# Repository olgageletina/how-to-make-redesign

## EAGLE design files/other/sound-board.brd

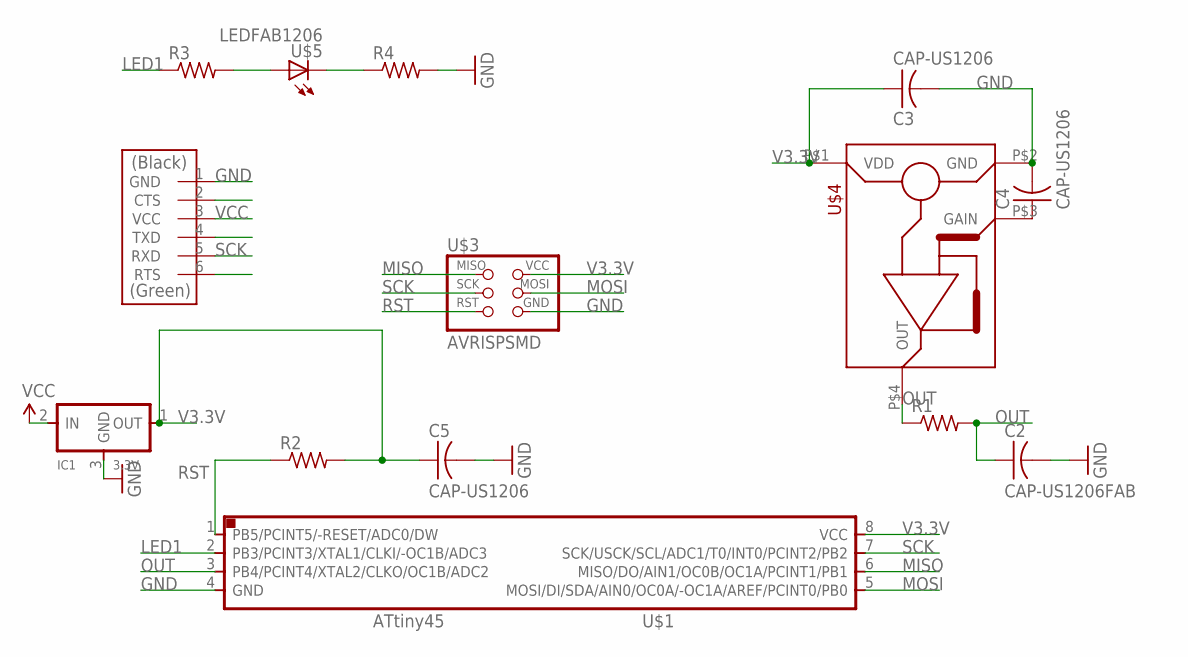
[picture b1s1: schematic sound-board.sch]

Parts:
C2: CAP-US1206FAB; C1206FAB
C3, C4, C5: CAP-US1206; C1206
IC1: 3.3V; SOT23
R1, R2: RES-US1206; R1206
R3, R4: RES-US1206FAB; R1206FAB
U$1: ATTINY45SI; SOIC8
U$2: FTDI-SMD-HEADER; 1X06SMD
U$3: AVRISPSMD; 2X03SMD
U$4: MEMS_MIC_SPU0414HR5H-SB; CSP-4PIN
U$5: LEDFAB1206; LED1206FAB

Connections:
GAIN: C4.1, U$4.P$3 (GAIN)
GND: C2.2, C3.2, C4.2, C5.2, IC1.3 (GND), R4.2, U$1.4 (GND), U$2.1 (GND), U$3.6 (GND), U$4.P$2 (GND)
LED1: R3.1, U$1.2 (PB3/PCINT3/XTAL1/CLKI/-OC1B/ADC3)
MISO: U$1.6 (MISO/DO/AIN1/OC0B/OC1A/PCINT1/PB1), U$3.1 (MISO)
MOSI: U$1.5 (MOSI/DI/SDA/AIN0/OC0A/-OC1A/AREF/PCINT0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), U$3.4 (MOSI)
unnamed: R3.2, U$5.1 (A)
unnamed: R4.1, U$5.2 (C)
OUT: C2.1, R1.1, R1.2, U$1.3 (PB4/PCINT4/XTAL2/CLKO/OC1B/ADC2), U$4.P$4 (OUT)
RST: R2.1, U$1.1 (PB5/PCINT5/-RESET/ADC0/DW), U$3.5 (RST)
SCK: U$1.7 (SCK/USCK/SCL/ADC1/T0/INT0/PCINT2/PB2), U$2.5 (RXD), U$3.3 (SCK)
V3.3V: C3.1, C5.1, IC1.1 (OUT), R2.2, U$1.8 (VCC), U$3.2 (VCC), U$4.P$1 (VDD)
VCC: IC1.2 (IN), U$2.3 (VCC)

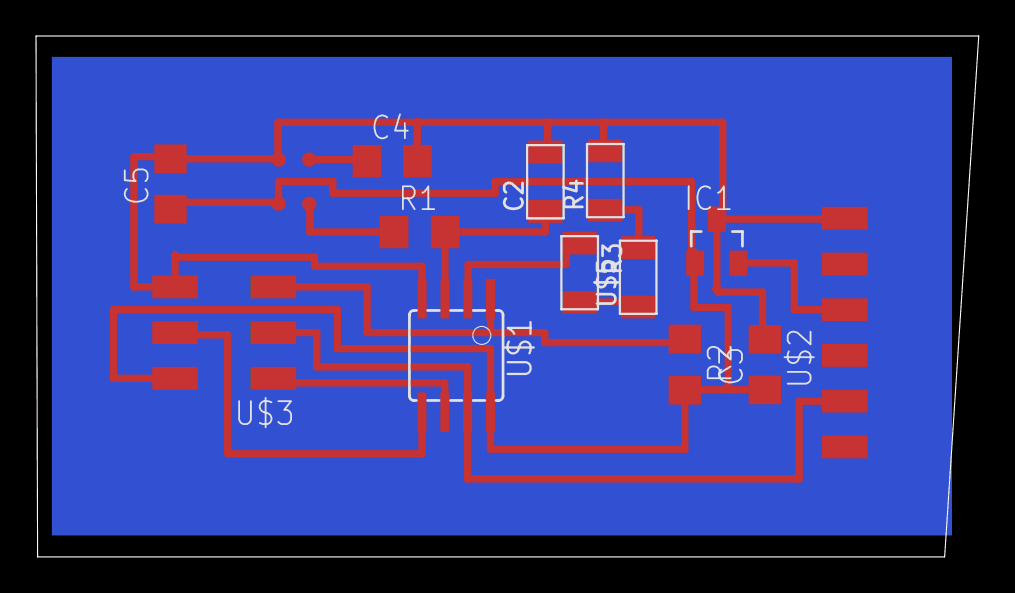
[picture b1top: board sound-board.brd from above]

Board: 2 copper layers, 52.4 x 28.9 mm, 14 parts (0 on the bottom side), 12 nets.

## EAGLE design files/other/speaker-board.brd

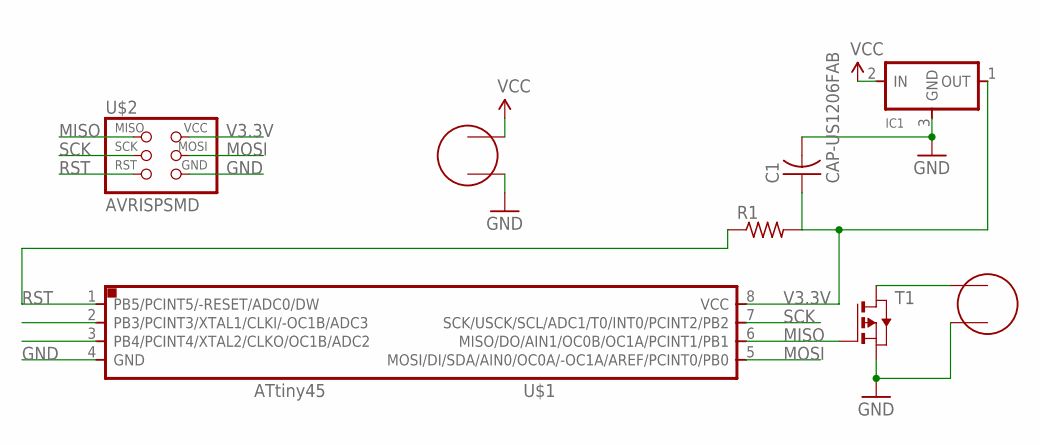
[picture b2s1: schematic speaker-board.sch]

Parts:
C1: CAP-US1206FAB; C1206FAB
IC1: REGULATORSOT23; SOT23
R1: RES-US1206FAB; R1206FAB
T1: PMOSFETSOT23; SOT-23
U$1: ATTINY45SI; SOIC8
U$2: AVRISPSMD; 2X03SMD
U$3, U$4: PINHD-2X1-SMD; 2X01SMD

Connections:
GND: C1.2, IC1.3 (GND), T1.2 (S), U$1.4 (GND), U$2.6 (GND), U$3.4, U$4.3
MISO: T1.3 (G), U$1.6 (MISO/DO/AIN1/OC0B/OC1A/PCINT1/PB1), U$2.1 (MISO)
MOSI: U$1.5 (MOSI/DI/SDA/AIN0/OC0A/-OC1A/AREF/PCINT0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), U$2.4 (MOSI)
unnamed: T1.1 (D), U$3.3
RST: R1.1, U$1.1 (PB5/PCINT5/-RESET/ADC0/DW), U$2.5 (RST)
SCK: U$1.7 (SCK/USCK/SCL/ADC1/T0/INT0/PCINT2/PB2), U$2.3 (SCK)
V3.3V: C1.1, IC1.1 (OUT), R1.2, U$1.8 (VCC), U$2.2 (VCC)
VCC: IC1.2 (IN), U$4.4

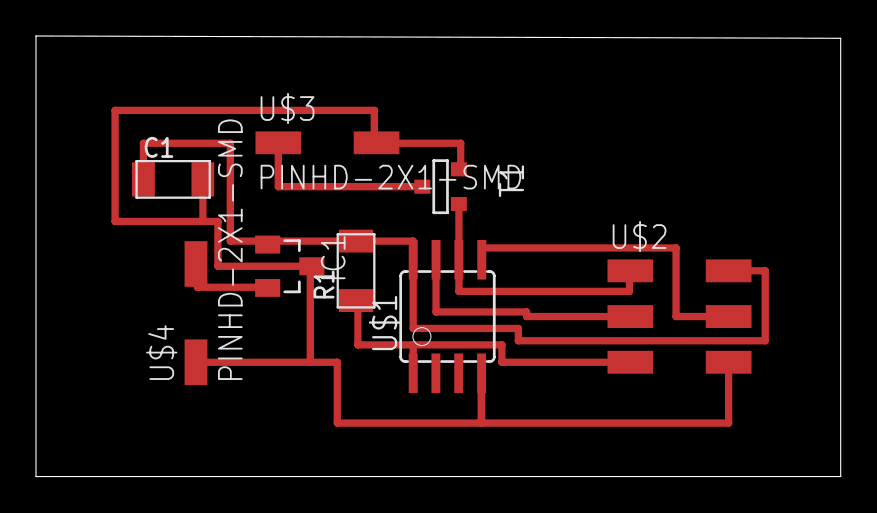
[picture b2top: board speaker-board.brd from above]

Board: 2 copper layers, 44.7 x 24.5 mm, 8 parts (0 on the bottom side), 8 nets.

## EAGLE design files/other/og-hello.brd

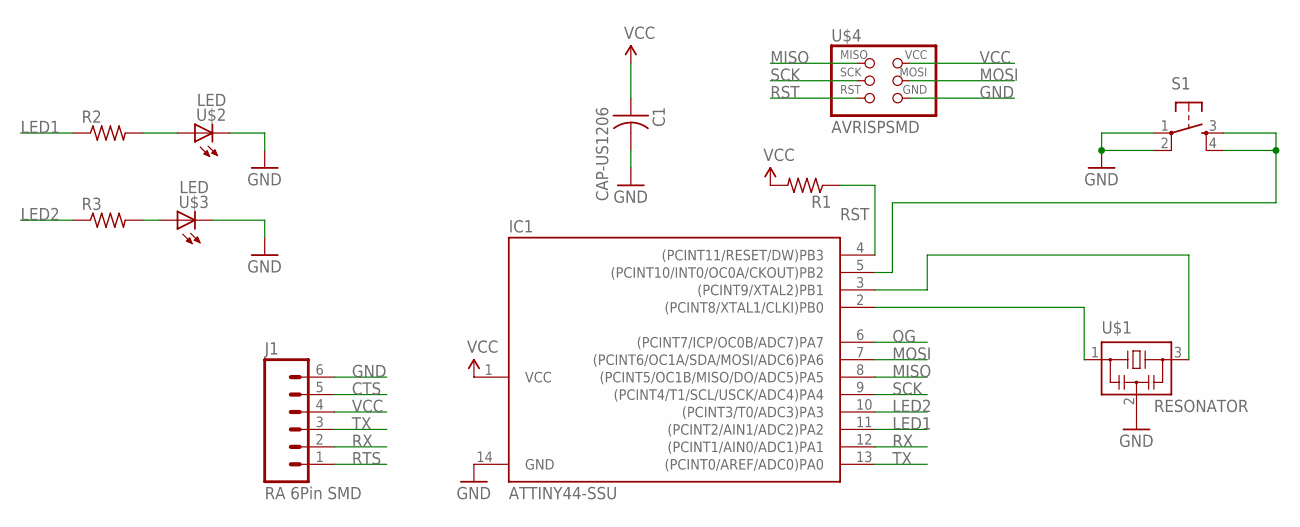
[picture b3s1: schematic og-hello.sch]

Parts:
C1: CAP-US1206; C1206
IC1: ATTINY44-SSU; SOIC14
J1: RA 6Pin SMD; 1X06-SMD
R1, R2, R3: RES-US1206; R1206
S1: 6MM_SWITCH6MM_SWITCH; 6MM_SWITCH
U$1: RESONATOR; EFOBM
U$2, U$3: LED; LED1206
U$4: AVRISPSMD; 2X03SMD

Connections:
CTS: J1.5
GND: C1.2, IC1.14 (GND), J1.6, S1.1, S1.2 (P1), U$1.2, U$2.2 (C), U$3.2 (C), U$4.6 (GND)
LED1: IC1.11 ((PCINT2/AIN1/ADC2)PA2), R2.1
LED2: IC1.10 ((PCINT3/T0/ADC3)PA3), R3.1
MISO: IC1.8 ((PCINT5/OC1B/MISO/DO/ADC5)PA5), U$4.1 (MISO)
MOSI: IC1.7 ((PCINT6/OC1A/SDA/MOSI/ADC6)PA6), U$4.4 (MOSI)
unnamed: IC1.3 ((PCINT9/XTAL2)PB1), U$1.3
unnamed: IC1.5 ((PCINT10/INT0/OC0A/CKOUT)PB2), S1.3 (S), S1.4 (S1)
unnamed: R3.2, U$3.1 (A)
unnamed: R2.2, U$2.1 (A)
unnamed: IC1.2 ((PCINT8/XTAL1/CLKI)PB0), U$1.1
OG: IC1.6 ((PCINT7/ICP/OC0B/ADC7)PA7)
RST: IC1.4 ((PCINT11/RESET/DW)PB3), R1.1, U$4.5 (RST)
RTS: J1.1
RX: IC1.12 ((PCINT1/AIN0/ADC1)PA1), J1.2
SCK: IC1.9 ((PCINT4/T1/SCL/USCK/ADC4)PA4), U$4.3 (SCK)
TX: IC1.13 ((PCINT0/AREF/ADC0)PA0), J1.3
VCC: C1.1, IC1.1 (VCC), J1.4, R1.2, U$4.2 (VCC)

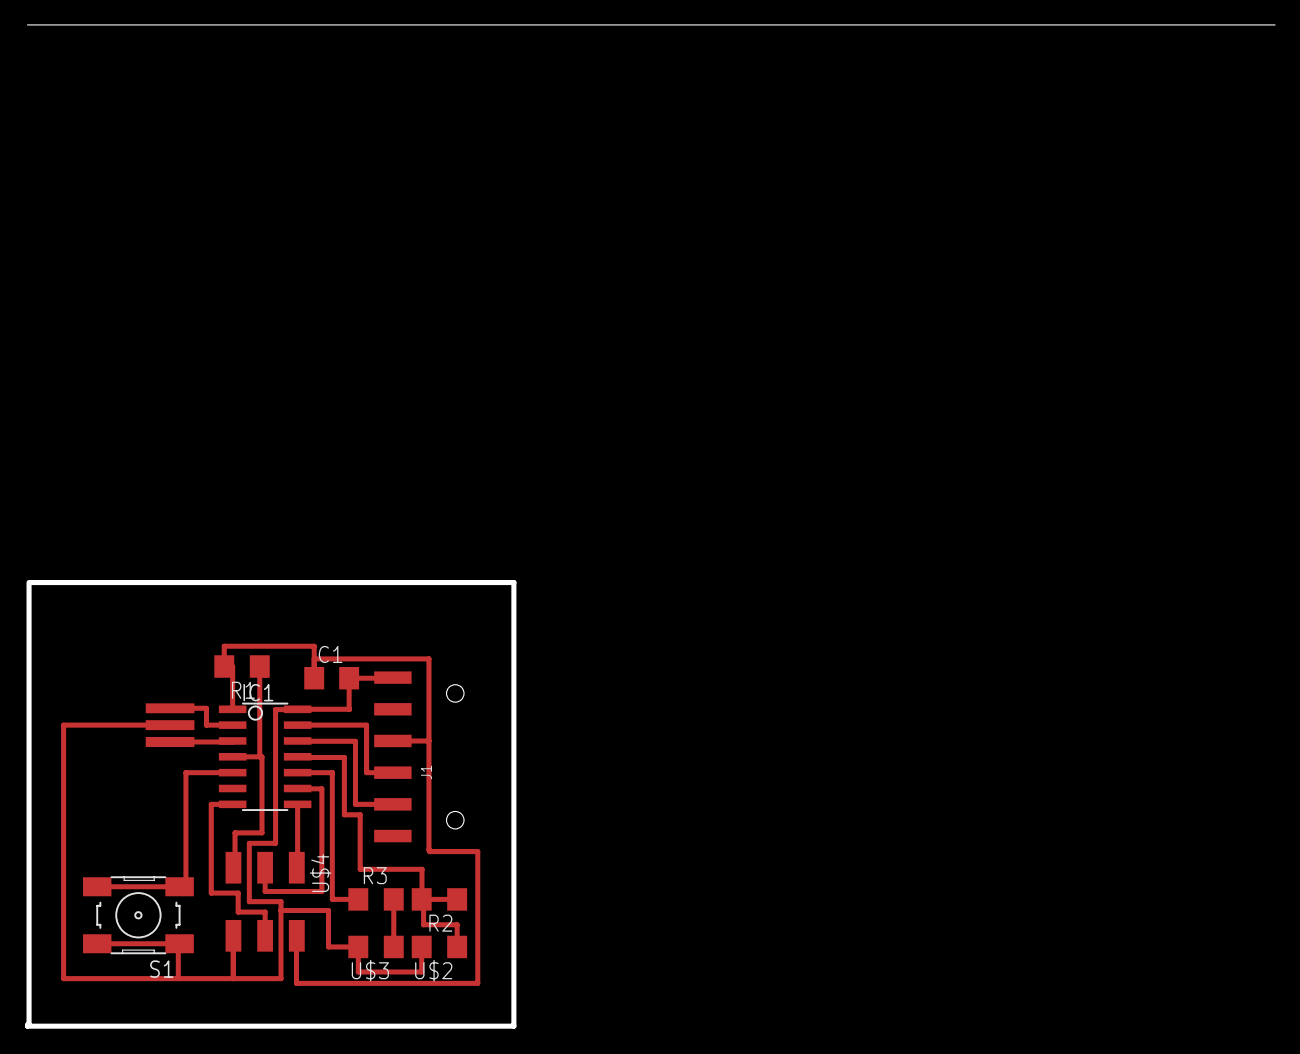
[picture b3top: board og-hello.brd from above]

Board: 2 copper layers, 39.0 x 35.6 mm, 11 parts (0 on the bottom side), 15 nets.

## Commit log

2022-09-27 adding some stuff
2022-10-02 maequee footer and definition sections done
2022-10-19 added week 1-2
2022-11-24 mobile and img clean up
2022-11-25 added menu animations
2022-11-25 mobile menu
2022-11-25 another couple of tweaks
2022-11-25 padding tweaks
2022-11-26 really not supposed to be committing on main by oh well
2022-11-26 final touches
2022-11-26 not sure why these files arw not being tracked
2022-11-26 tweaking mobile layout and padding
2022-11-26 tweaking links
2022-11-26 border radiusss
2022-11-27 mobile twaks
2022-12-09 edits edits edits
2022-12-14 updating CSS and LQI images
2022-12-14 cccccchanges
2023-01-11 added some copy changes fixed lqi images and refined menu behavior
2023-01-12 removing console logs and refining motion curves
2023-01-12 tweaking motion curves v2
2023-01-16 lqi-final-final-final
2024-09-02 editing some typos

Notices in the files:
parts and their libraries:
SparkFun-Connectors: Licensing: Creative Commons ShareAlike 4.0 International - https://creativecommons.org/licenses/by-sa/4.0
